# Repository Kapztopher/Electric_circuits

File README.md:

# Electric_circuits
 Various electronic circuits

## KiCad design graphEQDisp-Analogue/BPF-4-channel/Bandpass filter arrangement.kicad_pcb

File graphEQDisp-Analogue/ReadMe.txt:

GRAPHICS EQUALISER DISPLAY 

		All of the components are through hole as i haven't progressed to surface mount.
		
		These are the designs for a audial bandpass filter.  The circuits include the microphone pick-up, 
		basic signal proccessing, channel splitting, signal skimming and output.  

		The design is for a decoration that has backing lights as well, these are sequenced by a 555 circuit.
		The circuit for this is incorporated on a PCB with the switching transistors.  This was for simplicity
		and so I could have the pick-up and bandpass filters on the one PCB.

		Pick-up:	Microphone pickup with pick-up level controlled by a potentiometer, signal is then 
		passed through an op-amp to add signal gain.

		Basic signal proccessing:	Amplified signal from op-amp is passed though a zener diode 
		effectively capping and averaging the signal before being lifted back up to 10v.

		Channel splitting:	10v peak signal then goes through	50 - 280Hz 
										600 - 900Hz
										1.6 - 2.2kHz	
										3kHz+

		Signal skimming:	Each of the four bandpass filters passes it's signal to an op-amp
		stage that then only outputs high when the signal achieves threshold.

		BACKING LIGHT DISPLAY 
		
		LED backing lights sequence is derived from a 555 IC driving the clock to an CD4017BE johnson 
		counter.  The oscillating circuit is powered by an LM7805 so as reduce as much voltage 
		ripple as possible.  The 555 interferes terible with the microphone pick-up and is therfore 
		decoupled both at the 555 IC VDD and the power input.

		SWITCHING ARRAY

		2 ULN2003A's drive the LED's by switching earth,  any LED can be connect with a voltage 
		no more than 50 volts. LED's are not part of the circuit mearly an connector on the
		switching board.

		Bandpass filter runs on 10V any supply up to 50V can be used to drive LED's

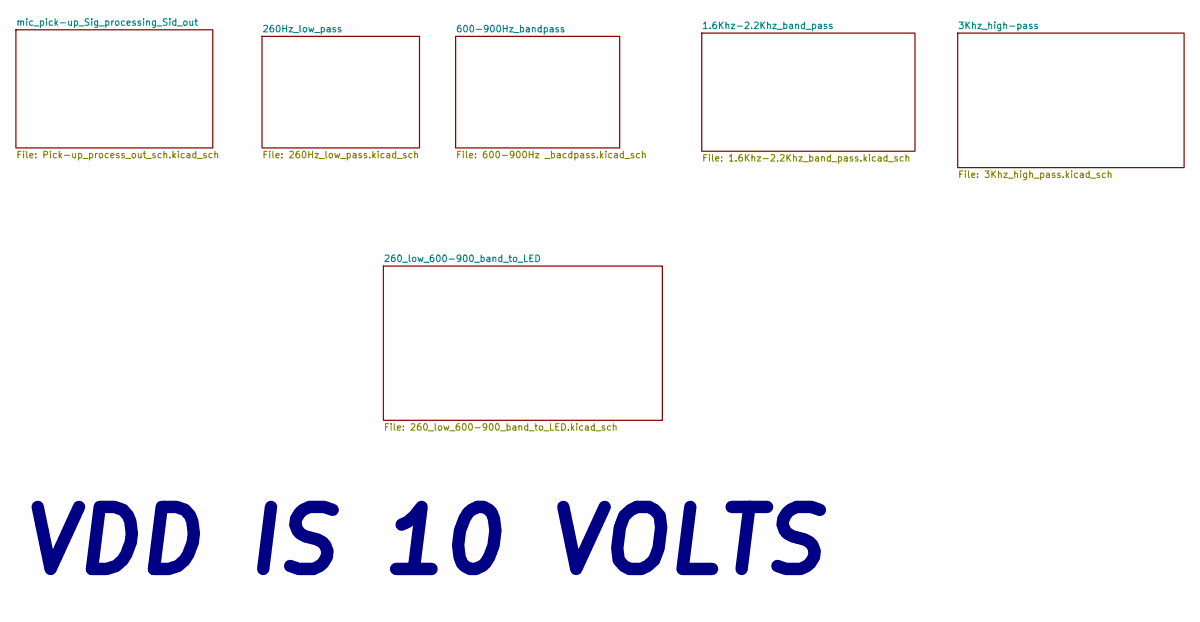
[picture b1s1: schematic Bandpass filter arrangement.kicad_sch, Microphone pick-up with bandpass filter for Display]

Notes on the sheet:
VDD IS 10 VOLTS

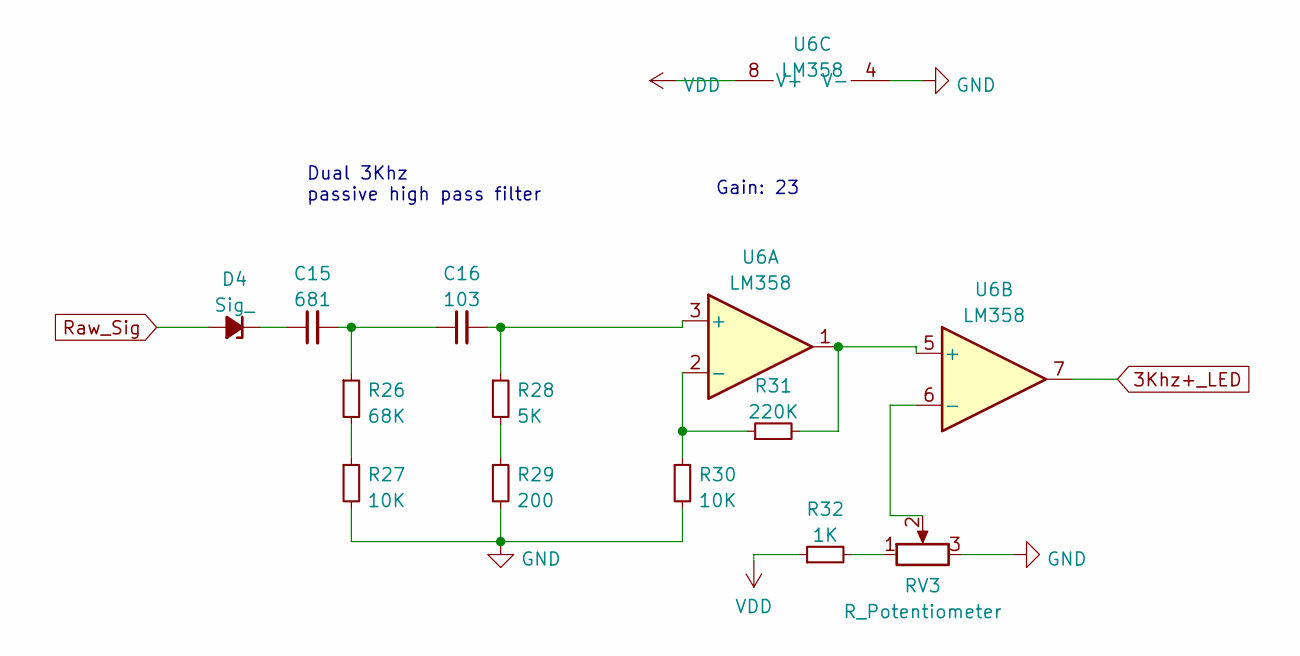
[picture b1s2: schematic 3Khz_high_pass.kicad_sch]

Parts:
C15: 681; C_Disc_D7.0mm_W2.5mm_P5.00mm
C16: 103; C_Disc_D7.0mm_W2.5mm_P5.00mm
D4: Sig_; D_DO-34_SOD68_P7.62mm_Horizontal
R26: 68K; R_Axial_DIN0204_L3.6mm_D1.6mm_P5.08mm_Horizontal
R27, R30: 10K; R_Axial_DIN0204_L3.6mm_D1.6mm_P5.08mm_Horizontal
R28: 5K; R_Axial_DIN0204_L3.6mm_D1.6mm_P5.08mm_Horizontal
R29: 200; R_Axial_DIN0204_L3.6mm_D1.6mm_P5.08mm_Horizontal
R31: 220K; R_Axial_DIN0204_L3.6mm_D1.6mm_P5.08mm_Horizontal
R32: 1K; R_Axial_DIN0204_L3.6mm_D1.6mm_P5.08mm_Horizontal
RV3: R_Potentiometer; Potentiometer_Bourns_3296W_Vertical
U6: LM358; DIP-8_W7.62mm

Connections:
3Khz+_LED: U6.7
GND: R27.2, R29.2, R30.2, RV3.3, U6.4 (V-); also elsewhere on the board
unnamed: C15.1, D4.1 (K)
unnamed: C15.2, C16.1, R26.1
unnamed: C16.2, R28.1, U6.3 (+)
unnamed: R26.2, R27.1
unnamed: R28.2, R29.1
unnamed: R30.1, R31.1, U6.2 (-)
unnamed: R31.2, U6.1, U6.5 (+)
unnamed: R32.2, RV3.1
unnamed: RV3.2, U6.6 (-)
Raw_Sig: D4.2 (A); also elsewhere on the board
VDD: R32.1, U6.8 (V+); also elsewhere on the board

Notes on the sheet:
Gain: 23
Dual 3Khz passive high pass filter

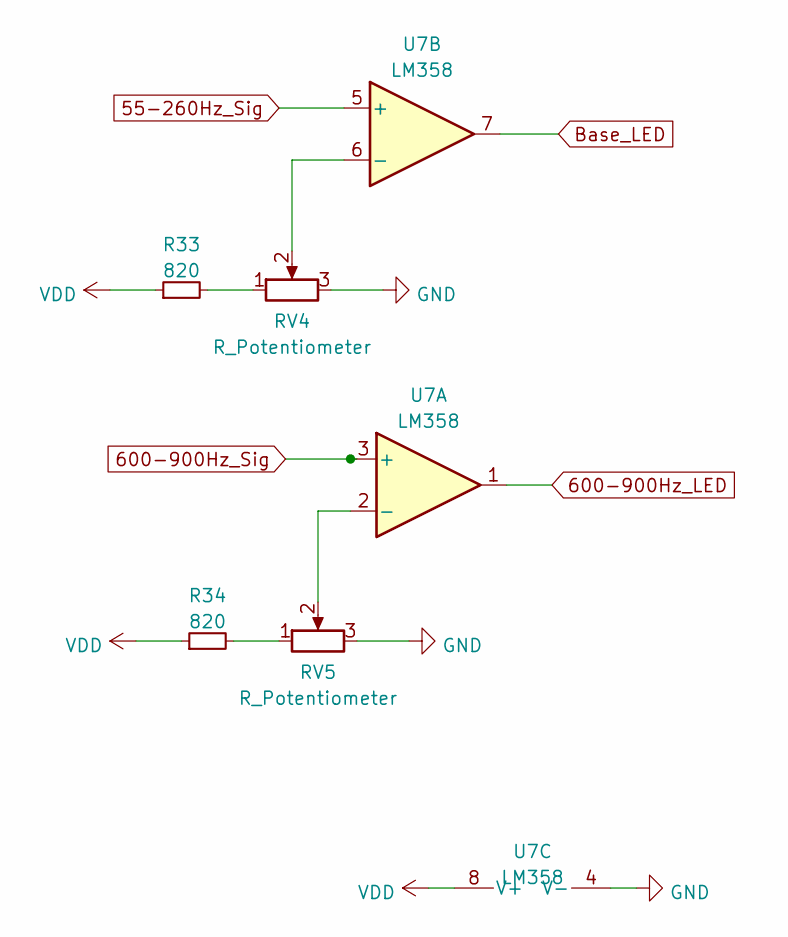
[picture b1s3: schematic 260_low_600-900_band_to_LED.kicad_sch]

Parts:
R33, R34: 820; R_Axial_DIN0204_L3.6mm_D1.6mm_P5.08mm_Horizontal
RV4, RV5: R_Potentiometer; Potentiometer_Bourns_3296W_Vertical
U7: LM358; DIP-8_W7.62mm

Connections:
55-260Hz_Sig: U7.5 (+); also elsewhere on the board
600-900Hz_LED: U7.1
600-900Hz_Sig: U7.3 (+); also elsewhere on the board
Base_LED: U7.7
GND: RV4.3, RV5.3, U7.4 (V-); also elsewhere on the board
unnamed: R33.2, RV4.1
unnamed: R34.2, RV5.1
unnamed: RV4.2, U7.6 (-)
unnamed: RV5.2, U7.2 (-)
VDD: R33.1, R34.1, U7.8 (V+); also elsewhere on the board

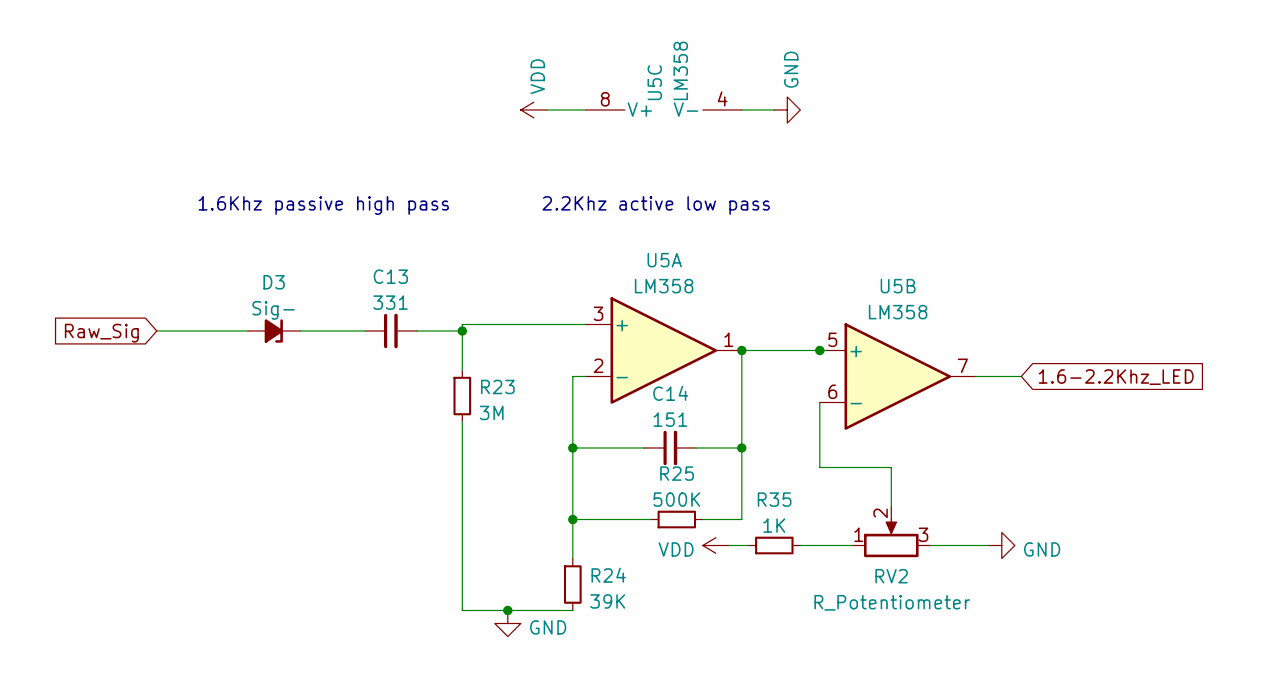
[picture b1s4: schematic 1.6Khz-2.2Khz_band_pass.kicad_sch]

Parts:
C13: 331; C_Disc_D7.0mm_W2.5mm_P5.00mm
C14: 151; C_Disc_D7.0mm_W2.5mm_P5.00mm
D3: Sig-; D_DO-34_SOD68_P7.62mm_Horizontal
R23: 3M; R_Axial_DIN0204_L3.6mm_D1.6mm_P5.08mm_Horizontal
R24: 39K; R_Axial_DIN0204_L3.6mm_D1.6mm_P5.08mm_Horizontal
R25: 500K; R_Axial_DIN0204_L3.6mm_D1.6mm_P5.08mm_Horizontal
R35: 1K; R_Axial_DIN0204_L3.6mm_D1.6mm_P5.08mm_Horizontal
RV2: R_Potentiometer; Potentiometer_Bourns_3296W_Vertical
U5: LM358; DIP-8_W7.62mm

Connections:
1.6-2.2Khz_LED: U5.7
GND: R23.2, R24.2, RV2.3, U5.4 (V-); also elsewhere on the board
unnamed: C13.1, D3.1 (K)
unnamed: C13.2, R23.1, U5.3 (+)
unnamed: C14.1, R24.1, R25.1, U5.2 (-)
unnamed: C14.2, R25.2, U5.1, U5.5 (+)
unnamed: R35.2, RV2.1
unnamed: RV2.2, U5.6 (-)
Raw_Sig: D3.2 (A); also elsewhere on the board
VDD: R35.1, U5.8 (V+); also elsewhere on the board

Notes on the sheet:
1.6Khz passive high pass
2.2Khz active low pass

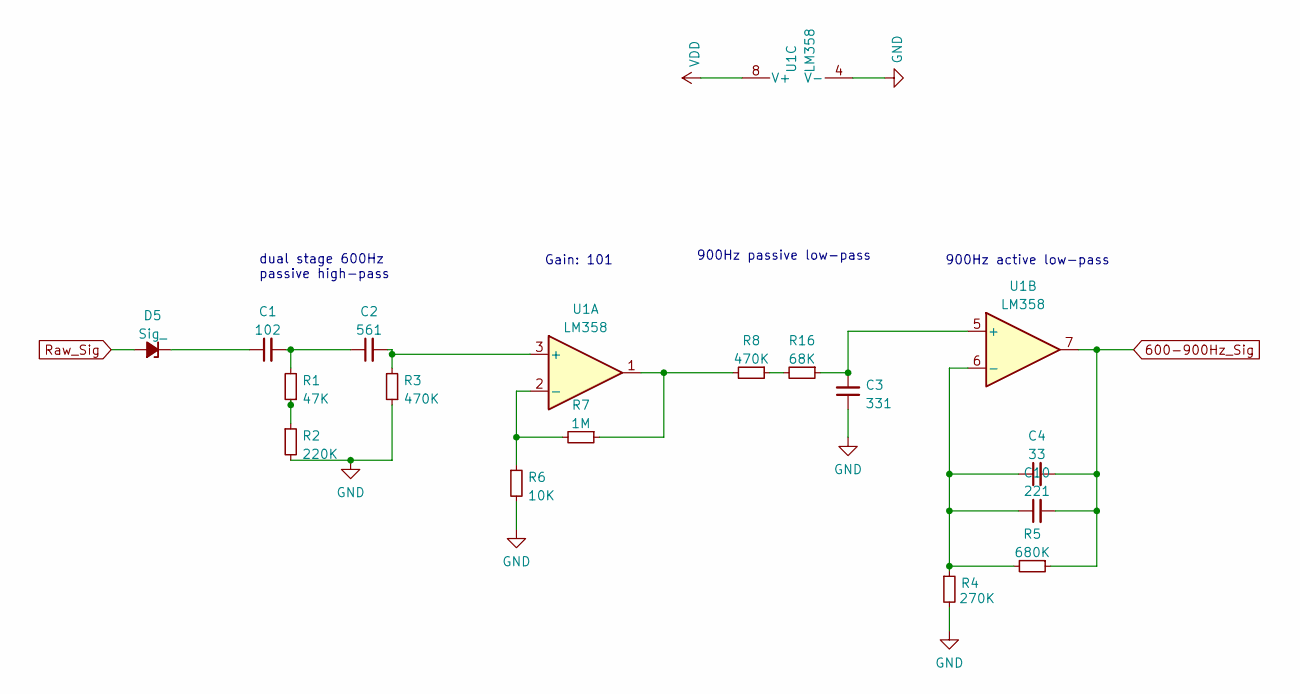
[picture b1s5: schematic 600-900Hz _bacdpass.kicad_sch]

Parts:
C1: 102; C_Disc_D7.0mm_W2.5mm_P5.00mm
C2: 561; C_Disc_D7.0mm_W2.5mm_P5.00mm
C3: 331; C_Disc_D7.0mm_W2.5mm_P5.00mm
C4: 33; C_Disc_D7.0mm_W2.5mm_P5.00mm
C10: 221; C_Disc_D7.0mm_W2.5mm_P5.00mm
D5: Sig_; D_DO-34_SOD68_P7.62mm_Horizontal
R1: 47K; R_Axial_DIN0204_L3.6mm_D1.6mm_P5.08mm_Horizontal
R2: 220K; R_Axial_DIN0204_L3.6mm_D1.6mm_P5.08mm_Horizontal
R3, R8: 470K; R_Axial_DIN0204_L3.6mm_D1.6mm_P5.08mm_Horizontal
R4: 270K; R_Axial_DIN0204_L3.6mm_D1.6mm_P5.08mm_Horizontal
R5: 680K; R_Axial_DIN0204_L3.6mm_D1.6mm_P5.08mm_Horizontal
R6: 10K; R_Axial_DIN0204_L3.6mm_D1.6mm_P5.08mm_Horizontal
R7: 1M; R_Axial_DIN0204_L3.6mm_D1.6mm_P5.08mm_Horizontal
R16: 68K; R_Axial_DIN0204_L3.6mm_D1.6mm_P5.08mm_Horizontal
U1: LM358; DIP-8_W7.62mm

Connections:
600-900Hz_Sig: C4.2, C10.2, R5.1, U1.7; also elsewhere on the board
GND: C3.1, R4.2, R6.2, U1.4 (V-); also elsewhere on the board
unnamed: C1.1, D5.1 (K)
unnamed: C1.2, C2.1, R1.2
unnamed: C2.2, R3.2, U1.3 (+)
unnamed: C3.2, R16.1, U1.5 (+)
unnamed: R1.1, R2.1
unnamed: R2.2, R3.1
unnamed: C4.1, C10.1, R4.1, R5.2, U1.6 (-)
unnamed: R8.1, R16.2
unnamed: R7.1, R8.2, U1.1
unnamed: R6.1, R7.2, U1.2 (-)
Raw_Sig: D5.2 (A); also elsewhere on the board
VDD: U1.8 (V+); also elsewhere on the board

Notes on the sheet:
dual stage 600Hz passive high-pass
900Hz passive low-pass
Gain: 101
900Hz active low-pass

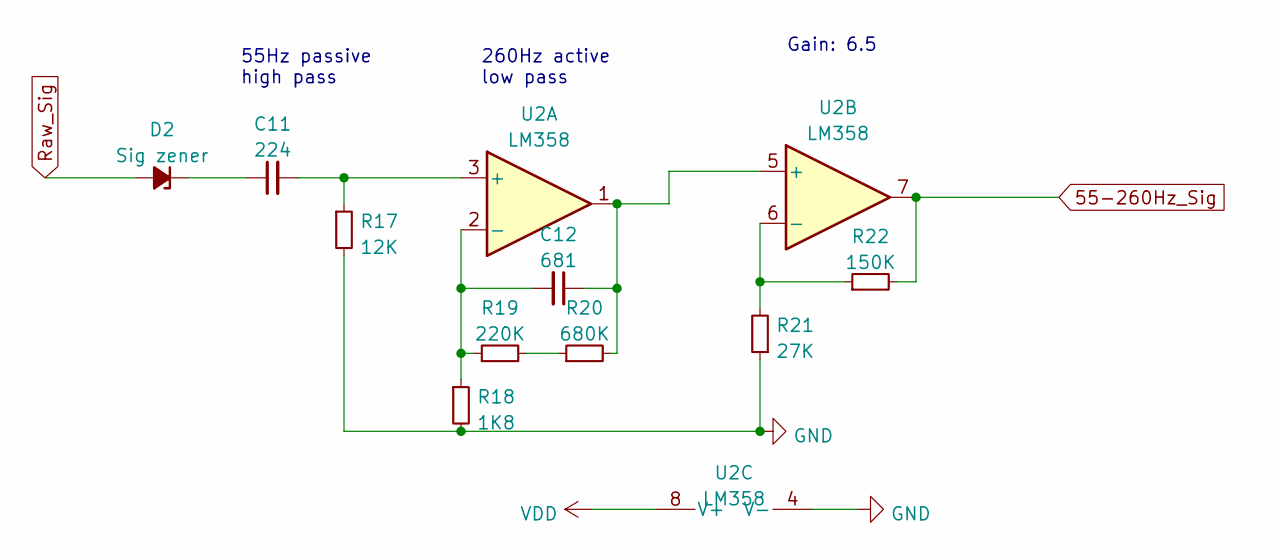
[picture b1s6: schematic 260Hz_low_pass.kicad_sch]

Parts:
C11: 224; C_Disc_D7.0mm_W2.5mm_P5.00mm
C12: 681; C_Disc_D7.0mm_W2.5mm_P5.00mm
D2: Sig zener; D_DO-34_SOD68_P7.62mm_Horizontal
R17: 12K; R_Axial_DIN0204_L3.6mm_D1.6mm_P5.08mm_Horizontal
R18: 1K8; R_Axial_DIN0204_L3.6mm_D1.6mm_P5.08mm_Horizontal
R19: 220K; R_Axial_DIN0204_L3.6mm_D1.6mm_P5.08mm_Horizontal
R20: 680K; R_Axial_DIN0204_L3.6mm_D1.6mm_P5.08mm_Horizontal
R21: 27K; R_Axial_DIN0204_L3.6mm_D1.6mm_P5.08mm_Horizontal
R22: 150K; R_Axial_DIN0204_L3.6mm_D1.6mm_P5.08mm_Horizontal
U2: LM358; DIP-8_W7.62mm

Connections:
55-260Hz_Sig: R22.2, U2.7; also elsewhere on the board
GND: R17.2, R18.2, R21.1, U2.4 (V-); also elsewhere on the board
unnamed: C11.1, D2.1 (K)
unnamed: C11.2, R17.1, U2.3 (+)
unnamed: C12.1, R20.2, U2.1, U2.5 (+)
unnamed: C12.2, R18.1, R19.1, U2.2 (-)
unnamed: R19.2, R20.1
unnamed: R21.2, R22.1, U2.6 (-)
Raw_Sig: D2.2 (A); also elsewhere on the board
VDD: U2.8 (V+); also elsewhere on the board

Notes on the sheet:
260Hz active low pass
Gain: 6.5
55Hz passive high pass

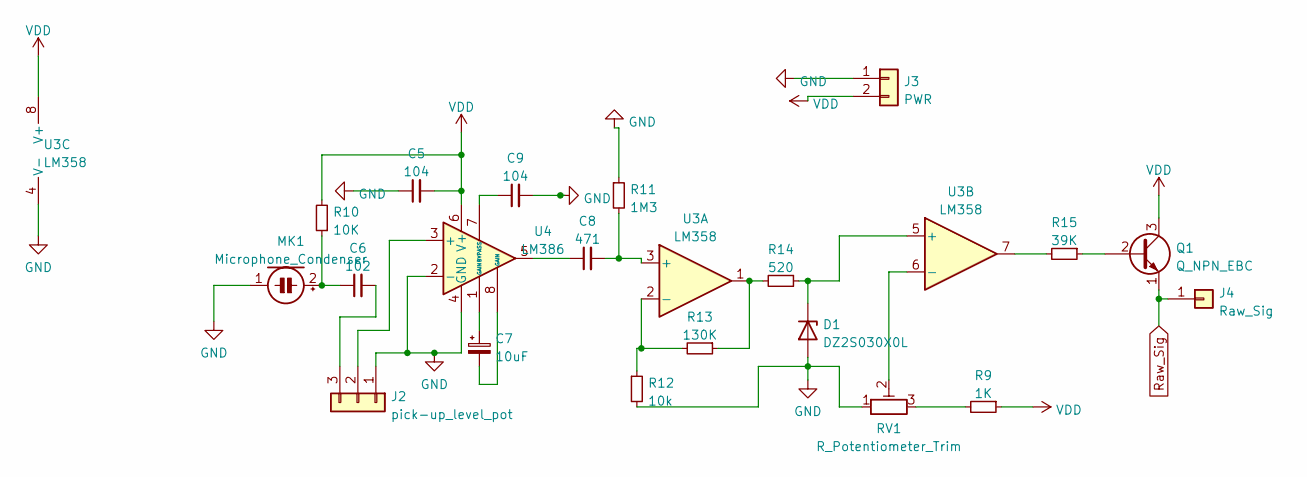
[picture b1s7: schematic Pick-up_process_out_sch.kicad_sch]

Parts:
C5, C9: 104; C_Disc_D7.0mm_W2.5mm_P5.00mm
C6: 102; C_Disc_D7.0mm_W2.5mm_P5.00mm
C7: 10uF; CP_Radial_D7.5mm_P2.50mm
C8: 471; C_Disc_D7.0mm_W2.5mm_P5.00mm
D1: DZ2S030X0L; D_DO-41_SOD81_P7.62mm_Horizontal
J2: pick-up_level_pot; PinHeader_1x03_P2.54mm_Vertical
J3: PWR; PinHeader_1x02_P2.54mm_Vertical
J4: Raw_Sig; PinHeader_1x01_P2.54mm_Vertical
MK1: Microphone_Condenser; PinHeader_1x02_P2.54mm_Vertical
Q1: Q_NPN_EBC; TO-92_HandSolder
R9: 1K; R_Axial_DIN0204_L3.6mm_D1.6mm_P5.08mm_Horizontal
R10: 10K; R_Axial_DIN0204_L3.6mm_D1.6mm_P5.08mm_Horizontal
R11: 1M3; R_Axial_DIN0204_L3.6mm_D1.6mm_P5.08mm_Horizontal
R12: 10k; R_Axial_DIN0204_L3.6mm_D1.6mm_P5.08mm_Horizontal
R13: 130K; R_Axial_DIN0204_L3.6mm_D1.6mm_P5.08mm_Horizontal
R14: 520; R_Axial_DIN0204_L3.6mm_D1.6mm_P5.08mm_Horizontal
R15: 39K; R_Axial_DIN0204_L3.6mm_D1.6mm_P5.08mm_Horizontal
RV1: R_Potentiometer_Trim; Potentiometer_Bourns_3296W_Vertical
U3: LM358; DIP-8_W7.62mm
U4: LM386; DIP-8_W7.62mm

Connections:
GND: C5.1, C9.2, D1.2 (A), J2.1, J3.1, MK1.1 (-), R11.1, R12.2, RV1.1, U3.4 (V-), U4.2 (-), U4.4 (GND); also elsewhere on the board
unnamed: C6.1, MK1.2 (+), R10.1
unnamed: C6.2, J2.3
unnamed: C7.1, U4.1 (GAIN)
unnamed: C7.2, U4.8 (GAIN)
unnamed: C8.1, U4.5
unnamed: C8.2, R11.2, U3.3 (+)
unnamed: C9.1, U4.7 (BYPASS)
unnamed: D1.1 (K), R14.1, U3.5 (+)
unnamed: J2.2, U4.3 (+)
unnamed: Q1.2 (B), R15.1
unnamed: R9.2, RV1.3
unnamed: R12.1, R13.2, U3.2 (-)
unnamed: R13.1, R14.2, U3.1
unnamed: R15.2, U3.7
unnamed: RV1.2, U3.6 (-)
Raw_Sig: J4.1, Q1.1 (E); also elsewhere on the board
VDD: C5.2, J3.2, Q1.3 (C), R9.1, R10.2, U3.8 (V+), U4.6 (V+); also elsewhere on the board

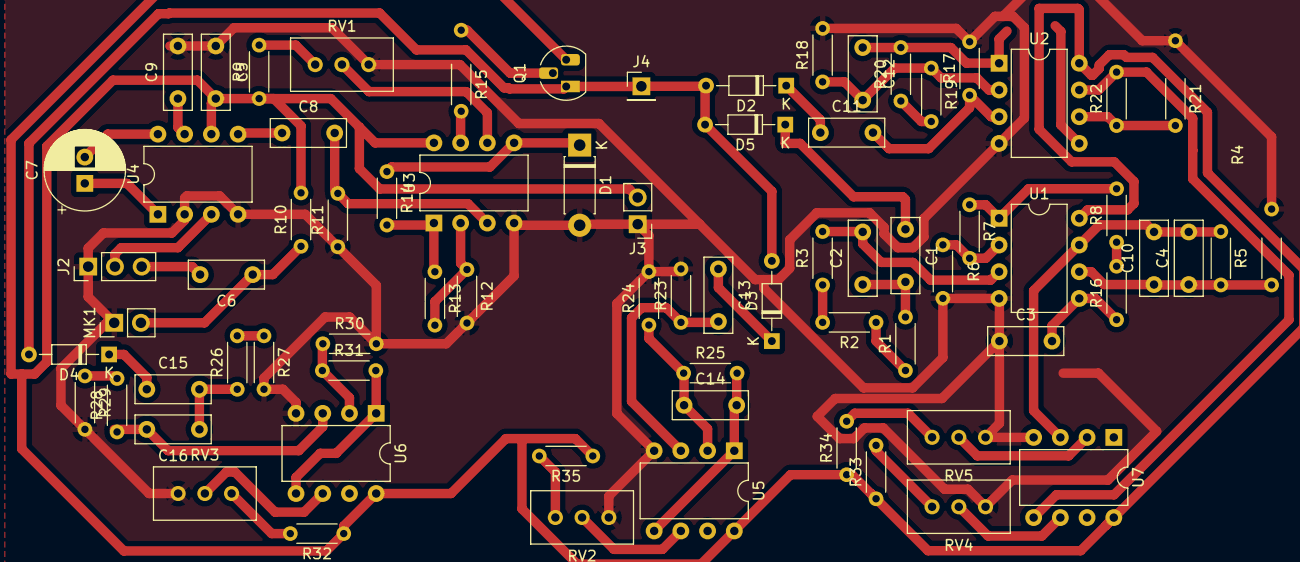
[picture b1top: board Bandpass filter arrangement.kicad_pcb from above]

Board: 2 copper layers, 73 parts (0 on the bottom side), 55 nets.

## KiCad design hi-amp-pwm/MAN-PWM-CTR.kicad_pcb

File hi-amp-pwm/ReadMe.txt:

HIGH AMPERAGE PWM DRIVER

A 555 IC controling a IRF540 mosfet and outputting a high source
current PWM signal,  Basically a DC motor speed controller, LED
dimmer control or what not.

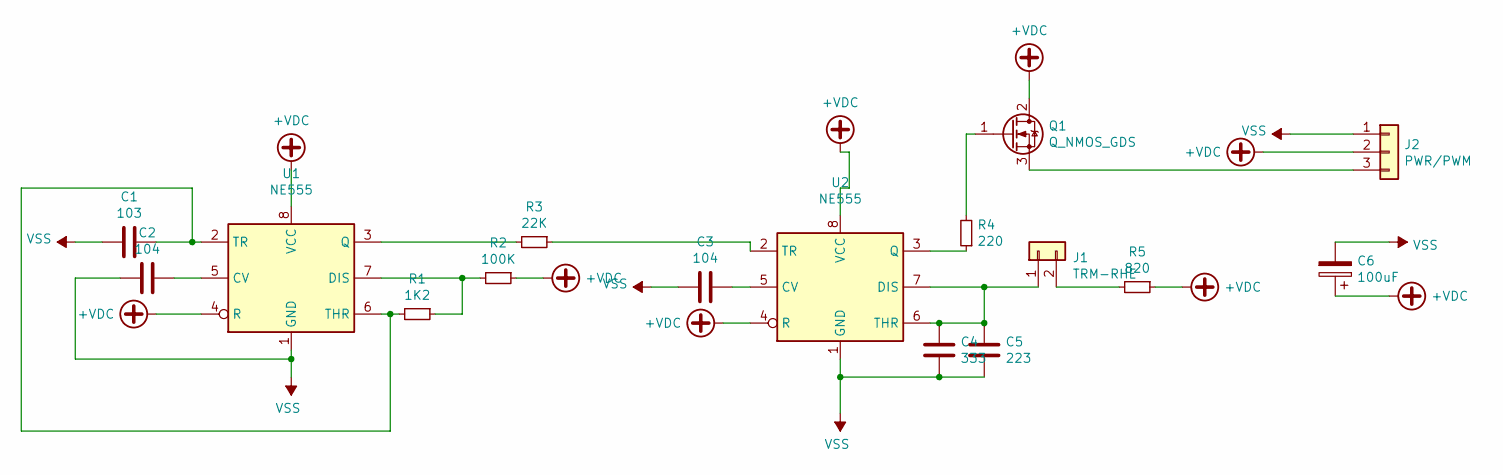
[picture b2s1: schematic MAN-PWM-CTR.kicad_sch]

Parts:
C1: 103; C_Disc_D4.3mm_W1.9mm_P5.00mm
C2, C3: 104; C_Disc_D4.3mm_W1.9mm_P5.00mm
C4: 333; C_Disc_D4.3mm_W1.9mm_P5.00mm
C5: 223; C_Disc_D4.3mm_W1.9mm_P5.00mm
C6: 100uF; C_Radial_D8.0mm_H7.0mm_P3.50mm
J1: TRM-RHE; PinHeader_1x02_P2.54mm_Vertical
J2: PWR/PWM; PinHeader_1x03_P2.54mm_Vertical
Q1: Q_NMOS_GDS; TO-220-3_Vertical
R1: 1K2; R_Axial_DIN0207_L6.3mm_D2.5mm_P7.62mm_Horizontal
R2: 100K; R_Axial_DIN0207_L6.3mm_D2.5mm_P7.62mm_Horizontal
R3: 22K; R_Axial_DIN0207_L6.3mm_D2.5mm_P7.62mm_Horizontal
R4: 220; R_Axial_DIN0207_L6.3mm_D2.5mm_P7.62mm_Horizontal
R5: 820; R_Axial_DIN0207_L6.3mm_D2.5mm_P7.62mm_Horizontal
U1, U2: NE555; DIP-8_W7.62mm

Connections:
+VDC: C6.1, J2.2, Q1.2 (D), R2.1, R5.1, U1.4 (R), U1.8 (VCC), U2.4 (R), U2.8 (VCC)
unnamed: C1.1, R1.2, U1.2 (TR), U1.6 (THR)
unnamed: C2.1, U1.5 (CV)
unnamed: C3.1, U2.5 (CV)
unnamed: C4.2, C5.2, J1.1, U2.6 (THR), U2.7 (DIS)
unnamed: J1.2, R5.2
unnamed: J2.3, Q1.3 (S)
unnamed: Q1.1 (G), R4.2
unnamed: R1.1, R2.2, U1.7 (DIS)
unnamed: R3.1, U2.2 (TR)
unnamed: R3.2, U1.3 (Q)
unnamed: R4.1, U2.3 (Q)
VSS: C1.2, C2.2, C3.2, C4.1, C5.1, C6.2, J2.1, U1.1 (GND), U2.1 (GND)

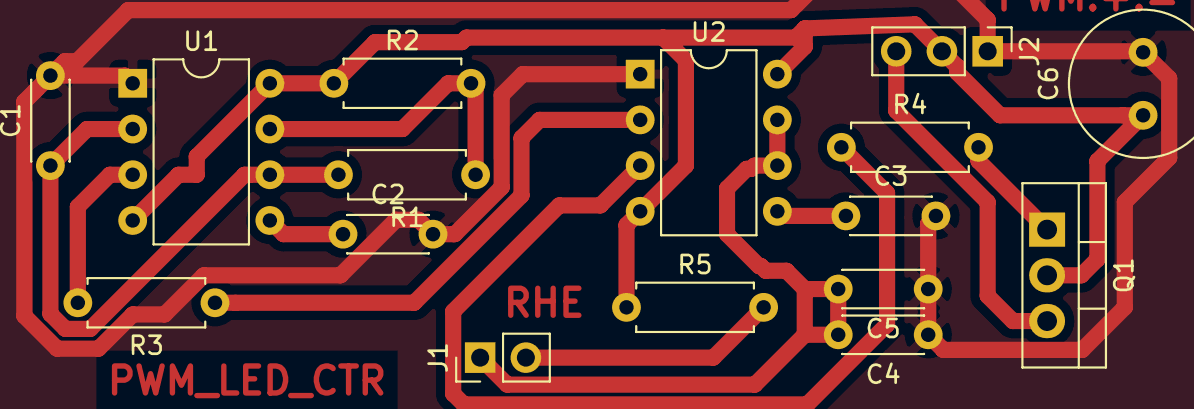
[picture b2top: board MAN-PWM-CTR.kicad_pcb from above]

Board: 2 copper layers, 16 parts (0 on the bottom side), 13 nets.

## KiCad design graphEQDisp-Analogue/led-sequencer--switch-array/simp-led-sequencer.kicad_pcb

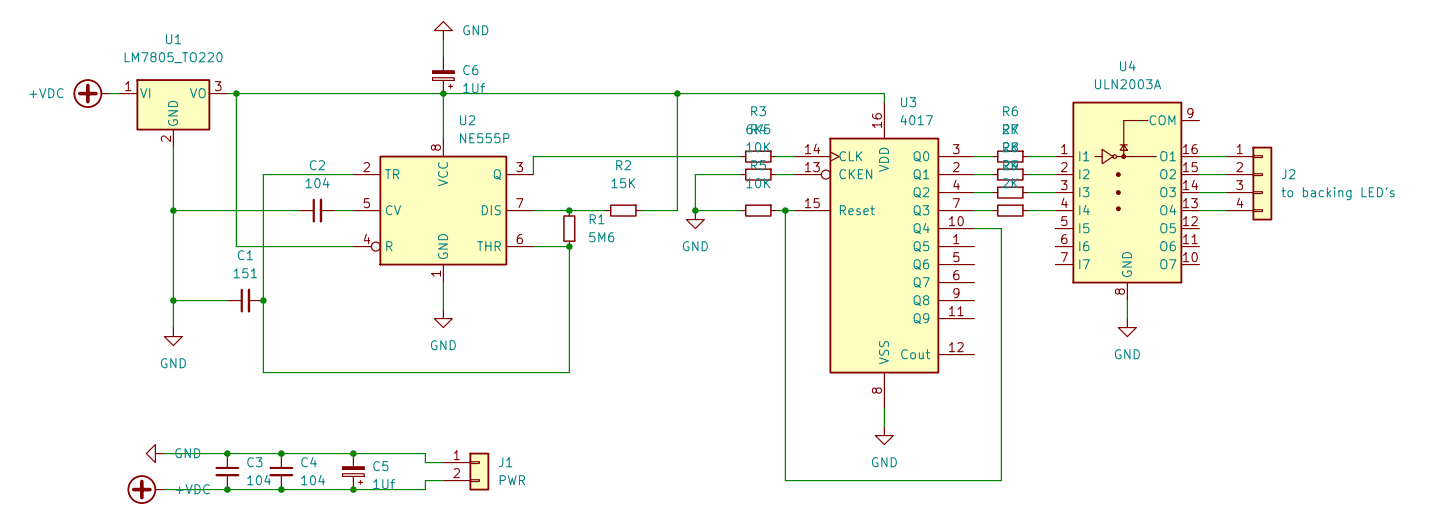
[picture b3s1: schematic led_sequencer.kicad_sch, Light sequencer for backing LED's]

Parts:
C1: 151; C_Disc_D5.0mm_W2.5mm_P5.00mm
C2, C3, C4: 104; C_Disc_D5.0mm_W2.5mm_P5.00mm
C5, C6: 1Uf; CP_Radial_D5.0mm_P2.50mm
J1: PWR; PinHeader_1x02_P2.54mm_Vertical
J2: to backing LED's; PinHeader_1x04_P2.54mm_Vertical
R1: 5M6; R_Axial_DIN0204_L3.6mm_D1.6mm_P7.62mm_Horizontal
R2: 15K; R_Axial_DIN0204_L3.6mm_D1.6mm_P7.62mm_Horizontal
R3: 6K5; R_Axial_DIN0204_L3.6mm_D1.6mm_P7.62mm_Horizontal
R4, R5: 10K; R_Axial_DIN0204_L3.6mm_D1.6mm_P7.62mm_Horizontal
R6, R7, R8, R9: 2K; R_Axial_DIN0204_L3.6mm_D1.6mm_P7.62mm_Horizontal
U1: LM7805_TO220; TO-220-3_Vertical
U2: NE555P; DIP-8_W7.62mm
U3: 4017; DIP-16_W7.62mm
U4: ULN2003A; DIP-16_W7.62mm

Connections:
+VDC: C3.2, C4.2, C5.1, J1.2, U1.1 (VI)
GND: C1.1, C2.1, C3.1, C4.1, C5.2, C6.2, J1.1, R4.2, R5.2, U1.2 (GND), U2.1 (GND), U3.8 (VSS), U4.8 (GND); also elsewhere on the board
unnamed: C1.2, R1.1, U2.2 (TR), U2.6 (THR)
unnamed: C2.2, U2.5 (CV)
unnamed: J2.1, U4.16 (O1)
unnamed: J2.2, U4.15 (O2)
unnamed: J2.3, U4.14 (O3)
unnamed: J2.4, U4.13 (O4)
unnamed: R1.2, R2.2, U2.7 (DIS)
unnamed: C6.1, R2.1, U1.3 (VO), U2.4 (R), U2.8 (VCC), U3.16 (VDD)
unnamed: R3.1, U3.14 (CLK)
unnamed: R3.2, U2.3 (Q)
unnamed: R4.1, U3.13 (CKEN)
unnamed: R5.1, U3.10 (Q4), U3.15 (Reset)
unnamed: R6.1, U4.1 (I1)
unnamed: R6.2, U3.3 (Q0)
unnamed: R7.1, U4.2 (I2)
unnamed: R7.2, U3.2 (Q1)
unnamed: R8.1, U4.3 (I3)
unnamed: R8.2, U3.4 (Q2)
unnamed: R9.1, U4.4 (I4)
unnamed: R9.2, U3.7 (Q3)

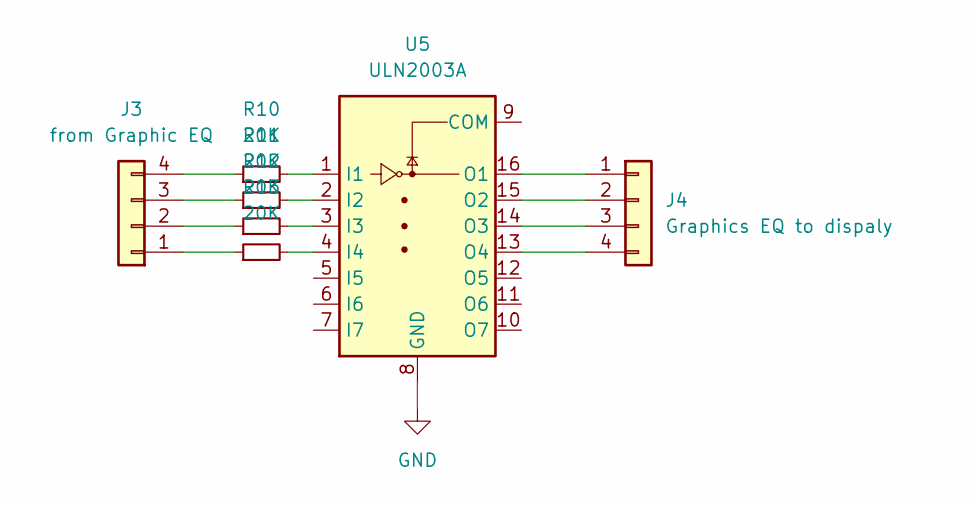
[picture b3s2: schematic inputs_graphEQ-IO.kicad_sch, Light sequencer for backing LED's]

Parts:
J3: from Graphic EQ; PinHeader_1x04_P2.54mm_Vertical
J4: Graphics EQ to dispaly; PinHeader_1x04_P2.54mm_Vertical
R10, R11, R12, R13: 20K; R_Axial_DIN0204_L3.6mm_D1.6mm_P7.62mm_Horizontal
U5: ULN2003A; DIP-16_W7.62mm

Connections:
GND: U5.8 (GND); also elsewhere on the board
unnamed: J3.1, R13.1
unnamed: J3.2, R12.1
unnamed: J3.3, R11.1
unnamed: J3.4, R10.1
unnamed: J4.1, U5.16 (O1)
unnamed: J4.2, U5.15 (O2)
unnamed: J4.3, U5.14 (O3)
unnamed: J4.4, U5.13 (O4)
unnamed: R10.2, U5.1 (I1)
unnamed: R11.2, U5.2 (I2)
unnamed: R12.2, U5.3 (I3)
unnamed: R13.2, U5.4 (I4)

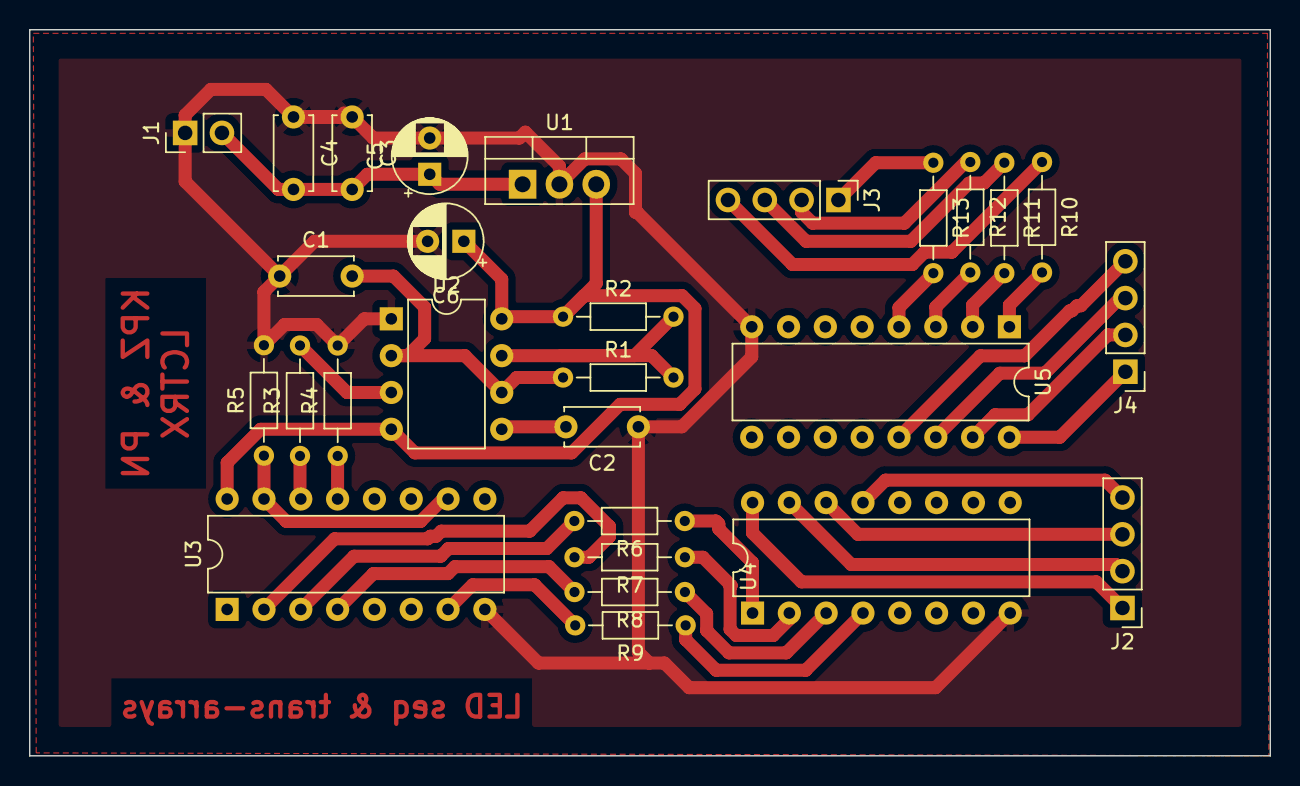
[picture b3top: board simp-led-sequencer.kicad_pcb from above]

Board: 2 copper layers, 85.6 x 50.1 mm, 28 parts (0 on the bottom side), 34 nets.

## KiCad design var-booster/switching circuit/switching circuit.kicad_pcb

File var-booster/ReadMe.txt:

VARIABLE BOOSTER

This circuit is for and booster with feedback. 
Using CMOS 555 and monolithic multivibrators a signal of 1.2mHz
is generated and fed to a switching inductor board.  The inductor 
board feeds back to the signal generating board, which uses an 
op-amp to compared the feedback signal and then control the 
switching and voltage supply level to the switching/inductor 
board.  This gives low power consumption & high voltage output.
delivers enough current to run a DC gearhead motor at about 30V
/ 400mA of a 12 volt supply.

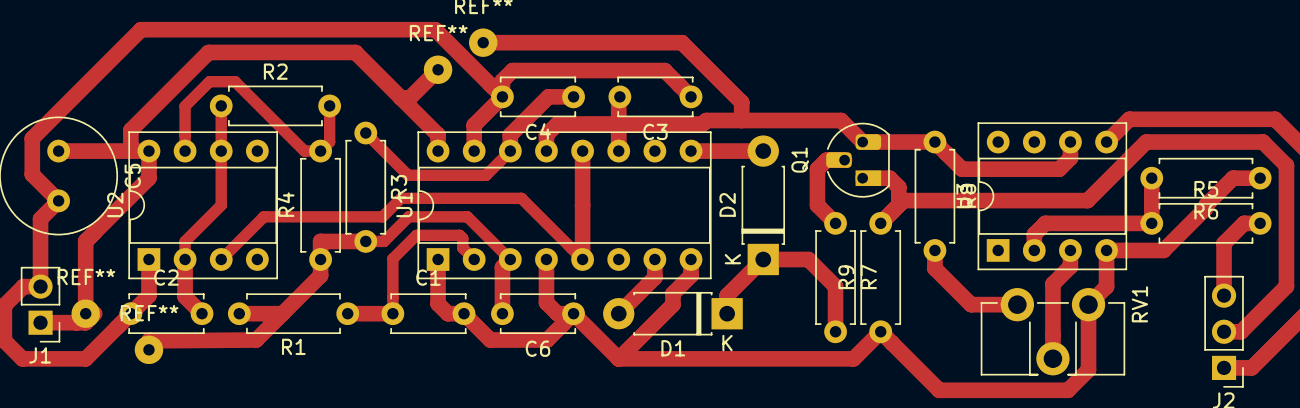
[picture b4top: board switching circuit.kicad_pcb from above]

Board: 2 copper layers, 24 parts (0 on the bottom side), 17 nets.

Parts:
C1, C2, C4: 101; C_Disc_D5.0mm_W2.5mm_P5.00mm
C3: 104; C_Disc_D5.0mm_W2.5mm_P5.00mm
C5: 100uF; C_Radial_D8.0mm_H7.0mm_P3.50mm
C6: 102; C_Disc_D5.0mm_W2.5mm_P5.00mm
D1, D2: D_Small; D_DO-41_SOD81_P7.62mm_Horizontal
J1: PWR; PinHeader_1x02_P2.54mm_Vertical
J2: SW CTR - F/B; PinHeader_1x03_P2.54mm_Vertical
Q1: PN100; TO-92_HandSolder
R1, R3, R6: 3K9; R_Axial_DIN0207_L6.3mm_D2.5mm_P7.62mm_Horizontal
R2: 5K; R_Axial_DIN0207_L6.3mm_D2.5mm_P7.62mm_Horizontal
R4: 270; R_Axial_DIN0207_L6.3mm_D2.5mm_P7.62mm_Horizontal
R5: 39K; R_Axial_DIN0207_L6.3mm_D2.5mm_P7.62mm_Horizontal
R7: 22K; R_Axial_DIN0207_L6.3mm_D2.5mm_P7.62mm_Horizontal
R8: 220; R_Axial_DIN0207_L6.3mm_D2.5mm_P7.62mm_Horizontal
R9: 330; R_Axial_DIN0207_L6.3mm_D2.5mm_P7.62mm_Horizontal
RV1: 10K; Potentiometer_ACP_CA9-H3,8_Horizontal
U1: 4098; DIP-16_W7.62mm_Socket
U2: LM555; DIP-8_W7.62mm_Socket
U3: LM386; DIP-8_W7.62mm_Socket

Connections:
FeedBack: J2.3, R5.2
unnamed: C1.1, R1.1, U1.2
unnamed: C2.2, R2.1, U2.2, U2.6
unnamed: C4.1, R3.1, U1.14
unnamed: D1.1, D2.1, R7.2
unnamed: D1.2, U1.7
unnamed: D2.2, U1.9
unnamed: Q1.2, R7.1
unnamed: R2.2, R4.2, U2.7
unnamed: R5.1, R6.2, U3.2
unnamed: R8.2, RV1.3
unnamed: RV1.2, U3.3
unnamed: U1.5, U1.12, U2.3
PWR-CTRL: J2.1, U3.5
SW-CTRL: J2.2, Q1.1, R9.2
VDD: C3.2, C5.1, C6.2, J1.1, Q1.3, R1.2, R3.2, R4.1, R8.1, U1.3, U1.11, U1.13, U1.16, U2.8, U3.6
VSS: C1.2, C2.1, C3.1, C4.2, C5.2, C6.1, J1.2, R6.1, R9.1, RV1.1, U1.1, U1.4, U1.8, U1.15, U2.1, U3.4

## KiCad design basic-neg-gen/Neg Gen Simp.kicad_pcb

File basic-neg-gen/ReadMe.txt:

Basic and simple negative voltage generator made for experimenting with circuits,  in particular attempts in removing voltage
			spikes.  Very low current supply capability.

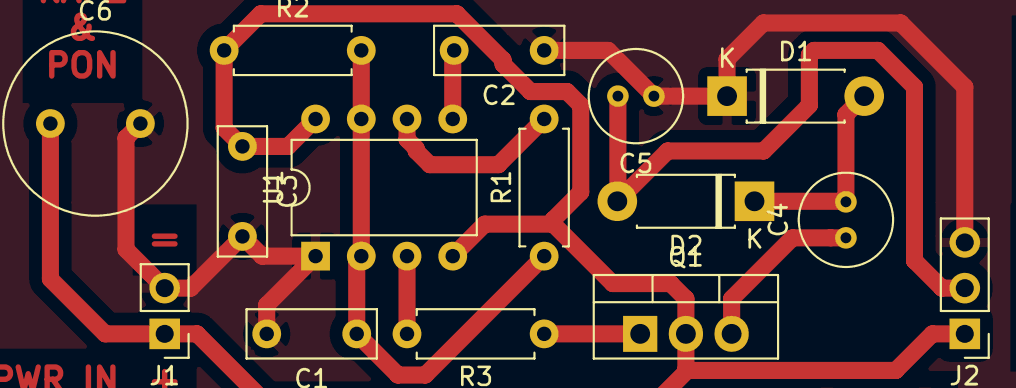
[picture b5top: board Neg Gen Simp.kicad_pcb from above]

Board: 2 copper layers, 15 parts (0 on the bottom side), 10 nets.

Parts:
C1: 223; C_Disc_D7.0mm_W2.5mm_P5.00mm
C2, C3: 104; C_Disc_D7.0mm_W2.5mm_P5.00mm
C4, C5: 10uF; C_Radial_D5.0mm_H7.0mm_P2.00mm
C6: 100uF; C_Radial_D10.0mm_H12.5mm_P5.00mm
D1, D2: D; D_DO-41_SOD81_P7.62mm_Horizontal
J1: PWR; PinHeader_1x02_P2.54mm_Vertical
J2: PWR OUT; PinHeader_1x03_P2.54mm_Vertical
Q1: Q_NMOS_GDS; TO-220-3_Vertical
R1: 2K; R_Axial_DIN0207_L6.3mm_D2.5mm_P7.62mm_Horizontal
R2: 2K2; R_Axial_DIN0207_L6.3mm_D2.5mm_P7.62mm_Horizontal
R3: 270; R_Axial_DIN0207_L6.3mm_D2.5mm_P7.62mm_Horizontal
U1: NE555; DIP-8_W7.62mm

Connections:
+VDC: C3.1, C6.1, J1.1, J2.1, Q1.2, R2.1, U1.4, U1.8
-VDC: C5.2, D2.2, J2.2
GND: C1.2, C2.1, C3.2, C5.1, C6.2, D1.1, J1.2, J2.3, U1.1
unnamed: C1.1, R1.1, R2.2, U1.2, U1.7
unnamed: C2.2, U1.5
unnamed: C4.1, Q1.3
unnamed: C4.2, D1.2, D2.1
unnamed: Q1.1, R3.1
unnamed: R1.2, U1.6
unnamed: R3.2, U1.3

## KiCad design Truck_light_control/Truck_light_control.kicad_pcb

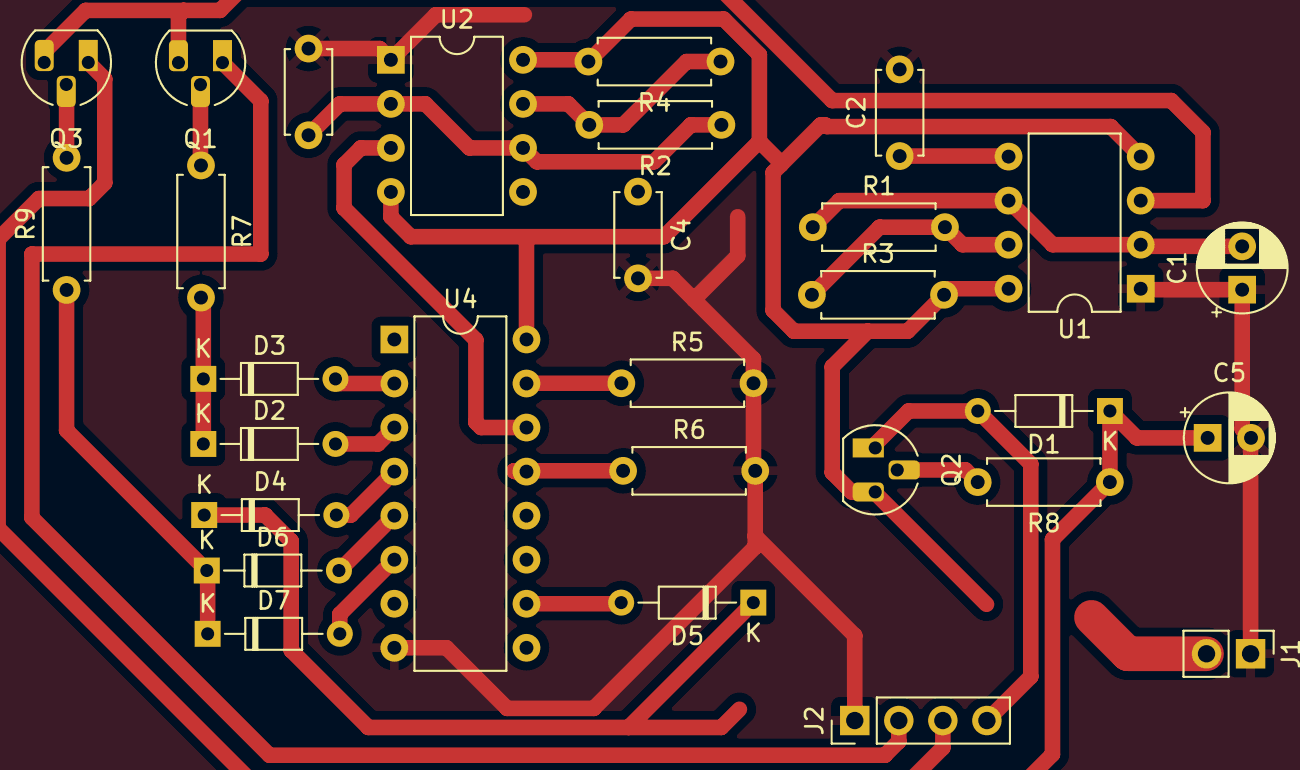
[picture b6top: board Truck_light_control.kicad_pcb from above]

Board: 2 copper layers, 29 parts (0 on the bottom side), 27 nets.

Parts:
C1, C5: C_Polarized; CP_Radial_D5.0mm_P2.50mm
C2, C3, C4: C; C_Disc_D4.7mm_W2.5mm_P5.00mm
D1, D2, D3, D4, D5, D6, D7: D_Small_Filled; D_DO-34_SOD68_P7.62mm_Horizontal
J1: Conn_01x02; PinHeader_1x02_P2.54mm_Vertical
J2: Conn_01x04; PinHeader_1x04_P2.54mm_Vertical
Q1, Q2, Q3: Q_NPN_EBC; TO-92_HandSolder
R1, R2, R3, R4, R5, R6, R7, R8, R9: R_Small; R_Axial_DIN0207_L6.3mm_D2.5mm_P7.62mm_Horizontal
U1, U2: NE555P; DIP-8_W7.62mm
U4: CD4017B; DIP-16_W7.62mm

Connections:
unnamed: C1.2, R1.1, U1.2 (TR), U1.6 (THR)
unnamed: C2.1, U1.5 (CV)
unnamed: C3.1, R2.1, U2.2 (TR), U2.6 (THR)
unnamed: C4.1, U2.5 (CV)
unnamed: C5.1, D1.1 (K), D4.1 (K), D5.1 (K), R8.1
unnamed: D1.2 (A), J2.4, Q2.1 (E)
unnamed: D2.1 (K), D3.1 (K), R7.2
unnamed: D2.2 (A), U4.3 (0)
unnamed: D3.2 (A), U4.2 (1)
unnamed: D4.2 (A), U4.4 (2)
unnamed: D5.2 (A), U4.10 (4)
unnamed: D6.1 (K), D7.1 (K), R9.1
unnamed: D6.2 (A), U4.5 (6)
unnamed: D7.2 (A), U4.6 (7)
unnamed: J2.2, Q1.1 (E)
unnamed: Q1.2 (B), R7.1
unnamed: Q2.2 (B), R8.2
unnamed: J2.3, Q3.1 (E)
unnamed: Q3.2 (B), R9.2
unnamed: R1.2, R3.1, U1.7 (DIS)
unnamed: R2.2, R4.1, U2.7 (DIS)
unnamed: R5.1, U4.15 (RST)
unnamed: R6.1, U4.13 (CLK_INHB)
unnamed: U2.3 (Q), U4.14 (CLK)
Turn_Signal: Q1.3 (C), Q3.3 (C), U1.3 (Q)
VDD: J1.2, Q2.3 (C), R3.2, R4.2, U1.4 (R), U1.8 (VCC), U2.4 (R), U2.8 (VCC), U4.16 (VDD)
VSS: C1.1, C2.2, C3.2, C4.2, C5.2, J1.1, J2.1, R5.2, R6.2, U1.1 (GND), U2.1 (GND), U4.8 (VSS)
